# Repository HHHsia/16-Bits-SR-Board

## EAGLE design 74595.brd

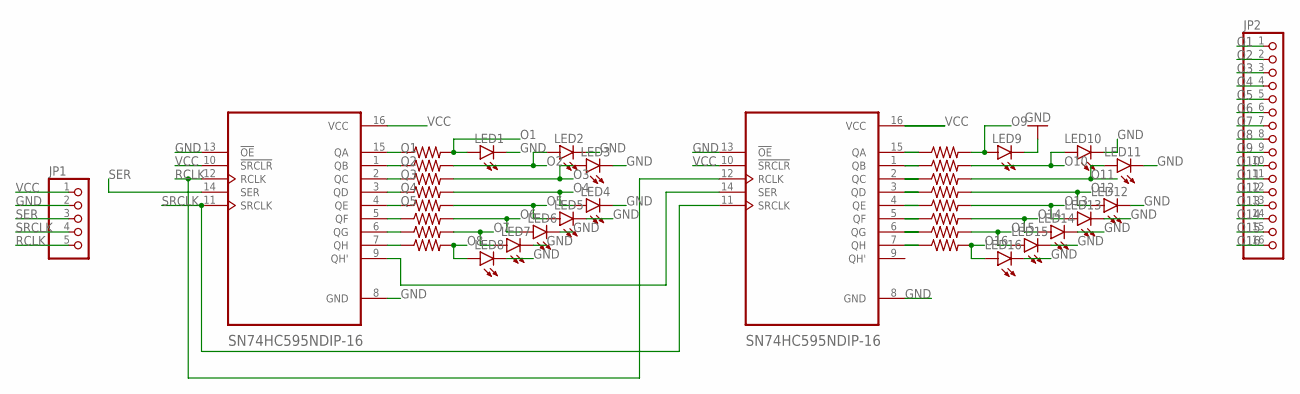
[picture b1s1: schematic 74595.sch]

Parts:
JP1: PINHD-1X5; 1X05
JP2: PINHD-1X16; 1X16
LED1, LED2, LED3, LED4, LED5, LED6, LED7, LED8, LED9, LED10, LED11, LED12, LED13, LED14, LED15, LED16: LEDCHIPLED_0805; CHIPLED_0805
R1, R2, R3, R4, R5, R6, R7, R8, R9, R10, R11, R12, R13, R14, R15, R16: R-US_R0805; R0805
U1, U2: SN74HC595NDIP-16; DIP794W45P254L1969H508Q16

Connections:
GND: JP1.2, LED1.C, LED2.C, LED3.C, LED4.C, LED5.C, LED6.C, LED7.C, LED8.C, LED9.C, LED10.C, LED11.C, LED12.C, LED13.C, LED14.C, LED15.C, LED16.C, U1.8 (GND), U1.13 (!OE), U2.8 (GND), U2.13 (!OE)
unnamed: U1.9 (QH'), U2.14 (SER)
O1: JP2.1, LED1.A, R1.2
O2: JP2.2, LED2.A, R2.2
O3: JP2.3, LED3.A, R3.2
O4: JP2.4, LED4.A, R4.2
O5: JP2.5, LED5.A, R5.2
O6: JP2.6, LED6.A, R6.2
O7: JP2.7, LED7.A, R8.2
O8: JP2.8, LED8.A, R9.2
O9: JP2.9, LED9.A, R7.2
O10: JP2.10, LED10.A, R10.2
O11: JP2.11, LED11.A, R11.2
O12: JP2.12, LED12.A, R12.2
O13: JP2.13, LED13.A, R13.2
O14: JP2.14, LED14.A, R14.2
O15: JP2.15, LED15.A, R15.2
O16: JP2.16, LED16.A, R16.2
Q1: R1.1, U1.15 (QA)
Q2: R2.1, U1.1 (QB)
Q3: R3.1, U1.2 (QC)
Q4: R4.1, U1.3 (QD)
Q5: R5.1, U1.4 (QE)
Q6: R6.1, U1.5 (QF)
Q7: R8.1, U1.6 (QG)
Q8: R9.1, U1.7 (QH)
Q9: R7.1, U2.15 (QA)
Q10: R10.1, U2.1 (QB)
Q11: R11.1, U2.2 (QC)
Q12: R12.1, U2.3 (QD)
Q13: R13.1, U2.4 (QE)
Q14: R14.1, U2.5 (QF)
Q15: R15.1, U2.6 (QG)
Q16: R16.1, U2.7 (QH)
RCLK: JP1.5, U1.12 (RCLK), U2.12 (RCLK)
SER: JP1.3, U1.14 (SER)
SRCLK: JP1.4, U1.11 (SRCLK), U2.11 (SRCLK)
VCC: JP1.1, U1.10 (!SRCLR), U1.16 (VCC), U2.10 (!SRCLR), U2.16 (VCC)

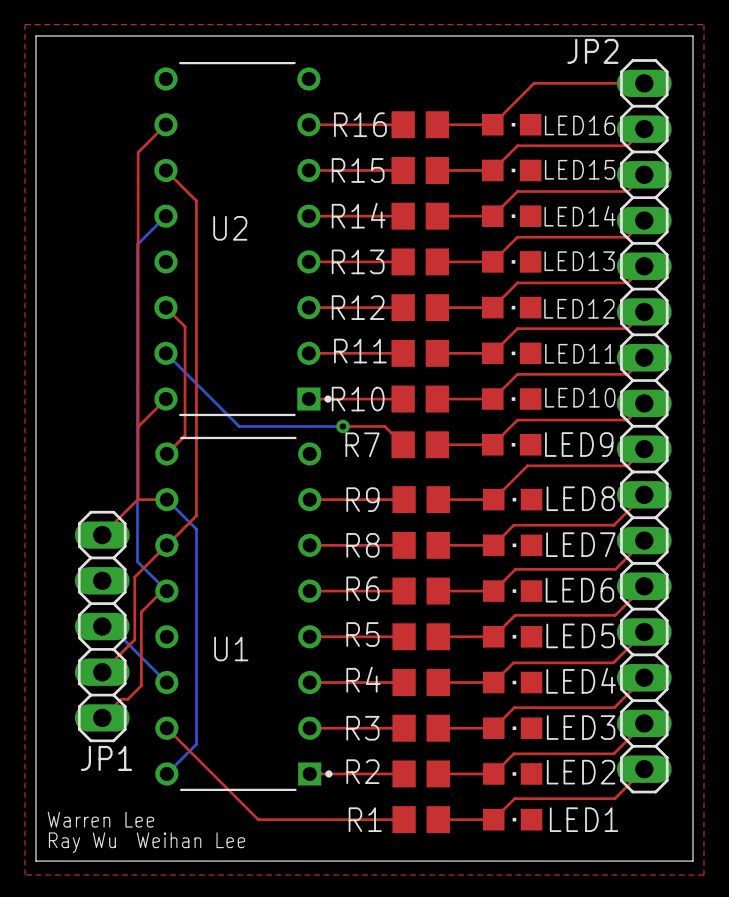
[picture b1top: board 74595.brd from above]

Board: 2 copper layers, 36.5 x 45.8 mm, 37 parts (1 on the bottom side), 38 nets.

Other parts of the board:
U$1: LOGO_SCALE_1.8

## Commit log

2024-07-05 20240705
2024-07-05 rename
